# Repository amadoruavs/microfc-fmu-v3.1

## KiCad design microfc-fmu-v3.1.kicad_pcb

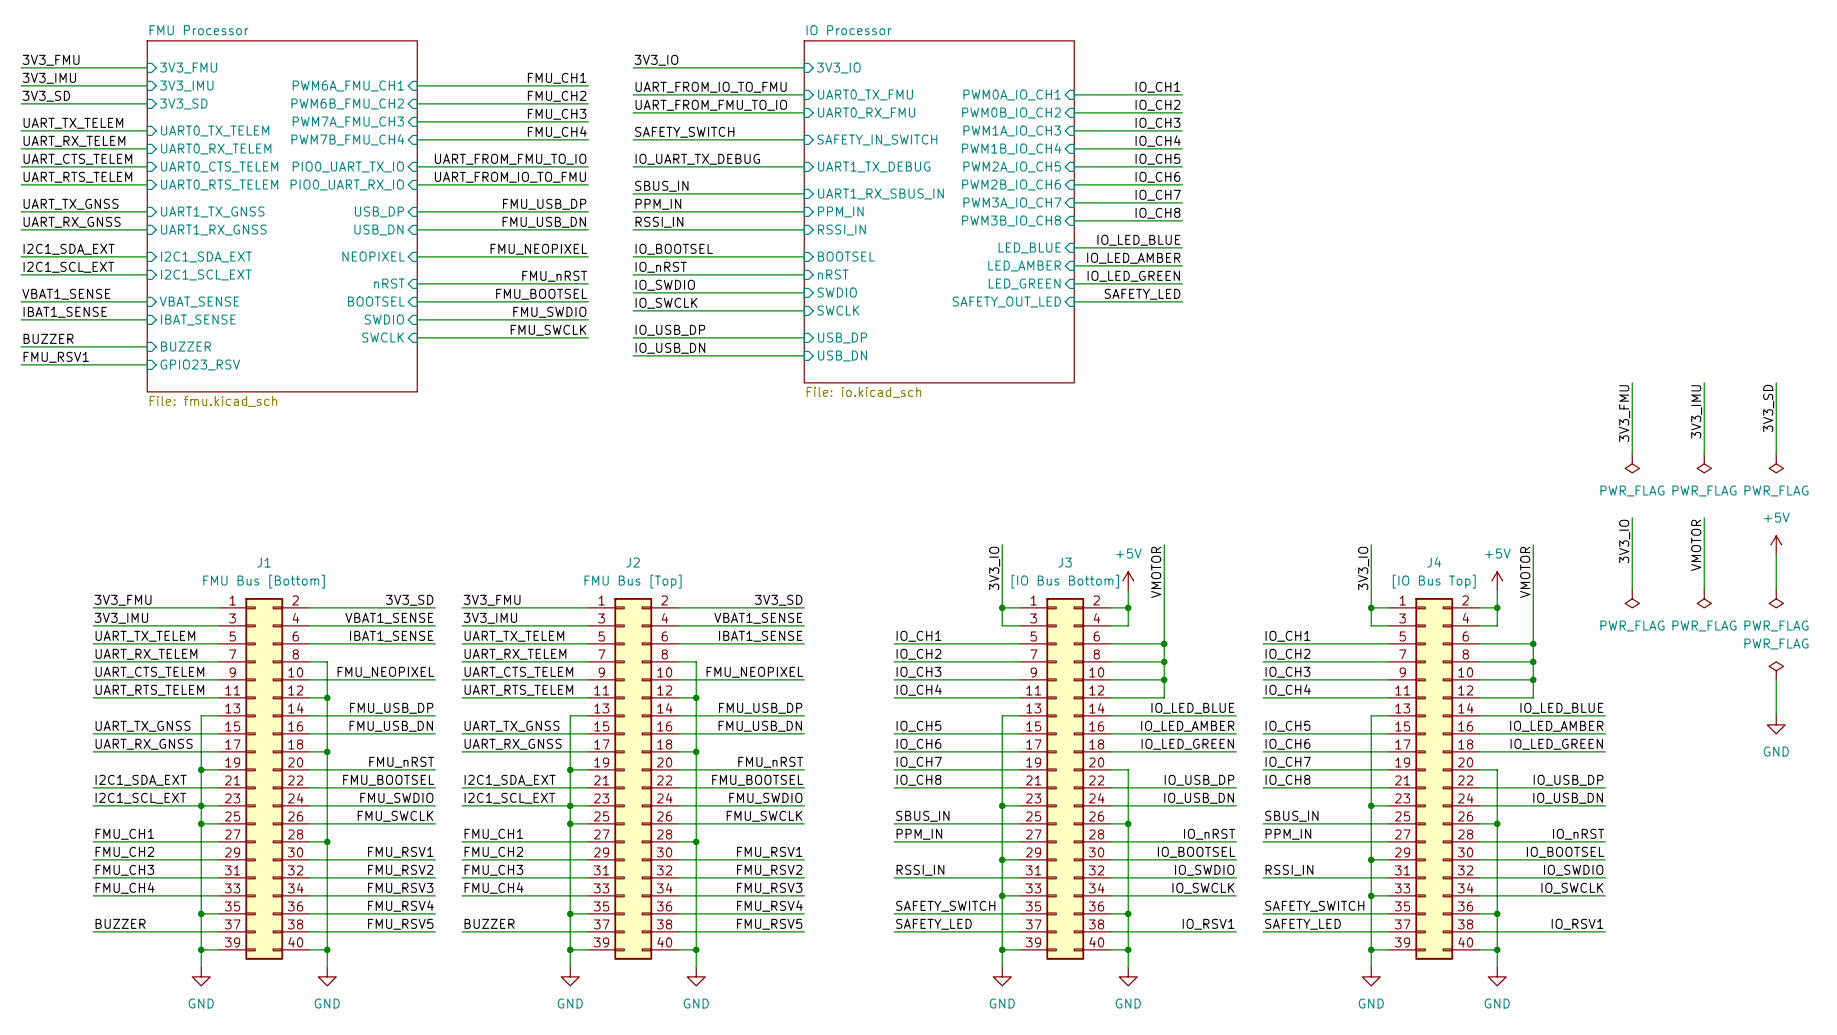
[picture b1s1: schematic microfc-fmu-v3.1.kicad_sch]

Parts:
J1: FMU Bus [Bottom]; HRS_DF40C-40DP-0.4V(51)
J2: FMU Bus [Top]; HIROSE_DF40C-40DS-0.4V(51)
J3: [IO Bus Bottom]; HRS_DF40C-40DP-0.4V(51)
J4: [IO Bus Top]; HIROSE_DF40C-40DS-0.4V(51)

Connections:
+5V: J3.2, J3.4, J4.2, J4.4
/3V3_FMU: J1.1, J2.1; also elsewhere on the board
/3V3_IMU: J1.3, J2.3; also elsewhere on the board
/3V3_IO: J3.1, J3.3, J4.1, J4.3; also elsewhere on the board
/3V3_SD: J1.2, J2.2; also elsewhere on the board
/BUZZER: J1.37, J2.37; also elsewhere on the board
/FMU_BOOTSEL: J1.22, J2.22; also elsewhere on the board
/FMU_CH1: J1.27, J2.27; also elsewhere on the board
/FMU_CH2: J1.29, J2.29; also elsewhere on the board
/FMU_CH3: J1.31, J2.31; also elsewhere on the board
/FMU_CH4: J1.33, J2.33; also elsewhere on the board
/FMU_NEOPIXEL: J1.10, J2.10; also elsewhere on the board
/FMU_RSV1: J1.30, J2.30; also elsewhere on the board
/FMU_RSV2: J1.32, J2.32
/FMU_RSV3: J1.34, J2.34
/FMU_RSV4: J1.36, J2.36
/FMU_RSV5: J1.38, J2.38
/FMU_SWCLK: J1.26, J2.26; also elsewhere on the board
/FMU_SWDIO: J1.24, J2.24; also elsewhere on the board
/FMU_USB_DN: J1.16, J2.16; also elsewhere on the board
/FMU_USB_DP: J1.14, J2.14; also elsewhere on the board
/FMU_nRST: J1.20, J2.20; also elsewhere on the board
/I2C1_SDA_EXT: J1.21, J2.21; also elsewhere on the board
/IO_BOOTSEL: J3.30, J4.30; also elsewhere on the board
/IO_CH1: J3.5, J4.5; also elsewhere on the board
/IO_CH2: J3.7, J4.7; also elsewhere on the board
/IO_CH3: J3.9, J4.9; also elsewhere on the board
/IO_CH4: J3.11, J4.11; also elsewhere on the board
/IO_CH5: J3.15, J4.15; also elsewhere on the board
/IO_CH6: J3.17, J4.17; also elsewhere on the board
/IO_CH7: J3.19, J4.19; also elsewhere on the board
/IO_CH8: J3.21, J4.21; also elsewhere on the board
/IO_LED_AMBER: J3.16, J4.16; also elsewhere on the board
/IO_LED_BLUE: J3.14, J4.14; also elsewhere on the board
/IO_LED_GREEN: J3.18, J4.18; also elsewhere on the board
/IO_RSV1: J3.38, J4.38
/IO_SWCLK: J3.34, J4.34; also elsewhere on the board
/IO_SWDIO: J3.32, J4.32; also elsewhere on the board
/IO_USB_DN: J3.24, J4.24; also elsewhere on the board
/IO_USB_DP: J3.22, J4.22; also elsewhere on the board
/IO_nRST: J3.28, J4.28; also elsewhere on the board
/PPM_IN: J3.27, J4.27; also elsewhere on the board
/RSSI_IN: J3.31, J4.31; also elsewhere on the board
/SAFETY_LED: J3.37, J4.37; also elsewhere on the board
/SAFETY_SWITCH: J3.35, J4.35; also elsewhere on the board
/SBUS_IN: J3.25, J4.25; also elsewhere on the board
/UART_CTS_TELEM: J1.9, J2.9; also elsewhere on the board
/UART_RTS_TELEM: J1.11, J2.11; also elsewhere on the board
/UART_RX_GNSS: J1.17, J2.17; also elsewhere on the board
/UART_RX_TELEM: J1.7, J2.7; also elsewhere on the board
/UART_TX_GNSS: J1.15, J2.15; also elsewhere on the board
/UART_TX_TELEM: J1.5, J2.5; also elsewhere on the board
/VMOTOR: J3.6, J3.8, J3.10, J3.12, J4.6, J4.8, J4.10, J4.12

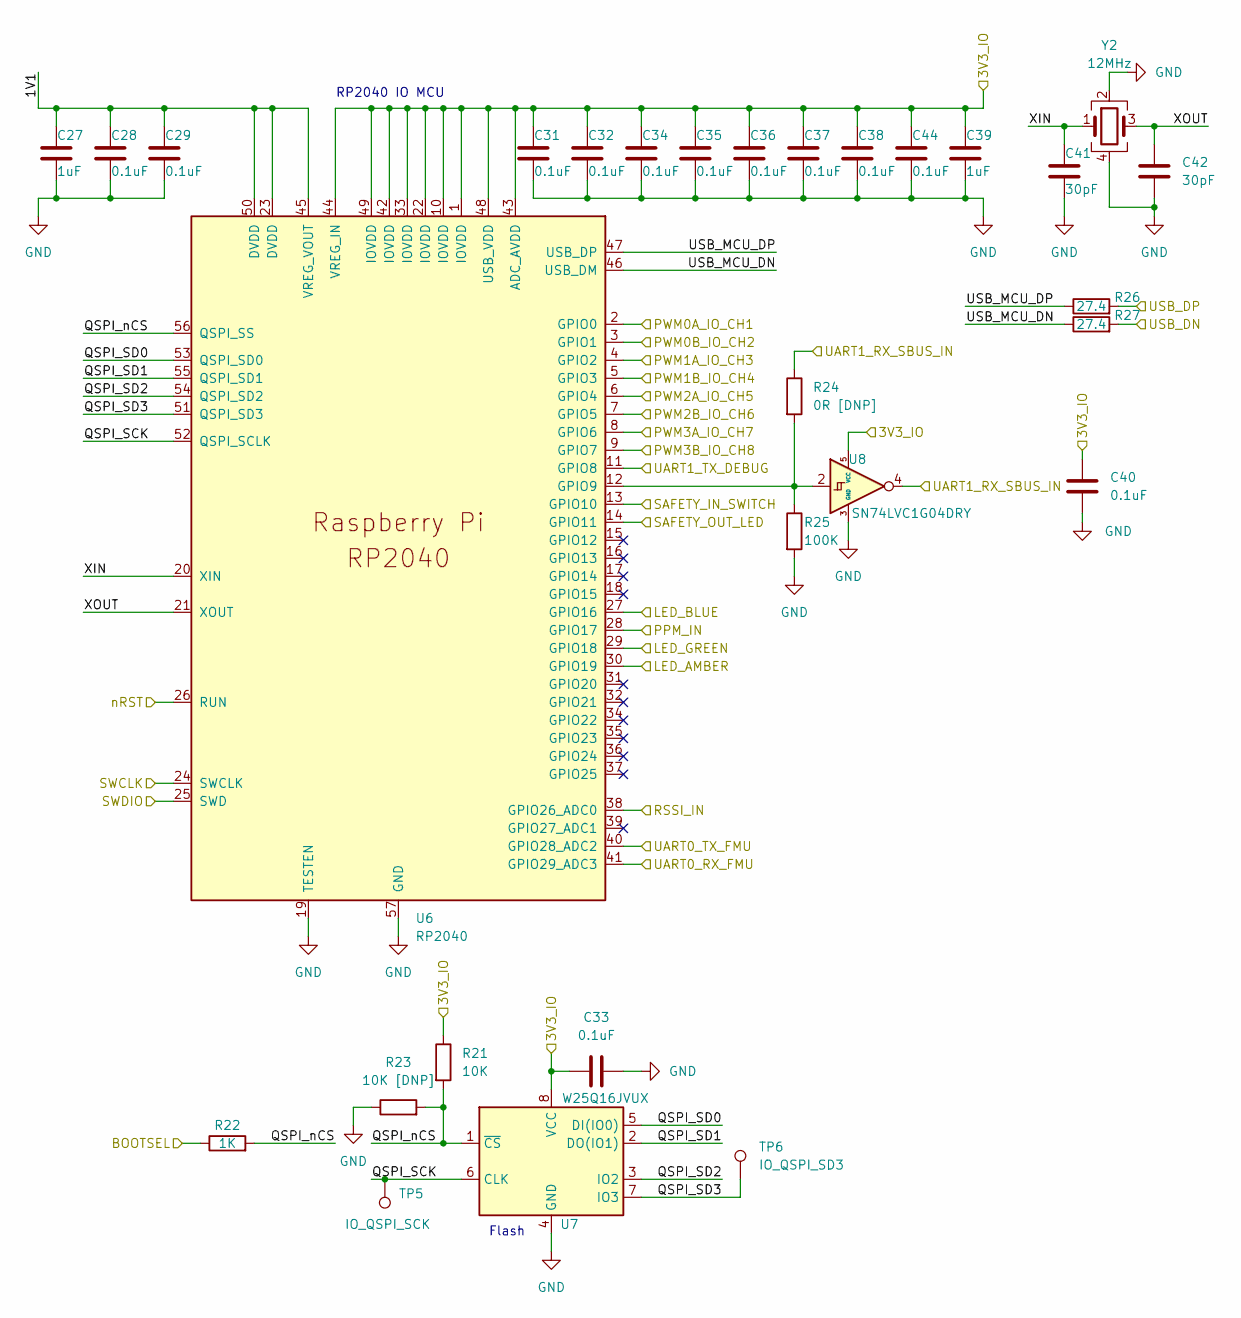
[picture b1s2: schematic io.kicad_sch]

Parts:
C27, C39: 1uF; C_0402_1005Metric; LCSC C52923
C28, C29, C31, C32, C33, C34, C35, C36, C37, C38, C44: 0.1uF; C_0402_1005Metric; LCSC C1525
C40: 0.1uF; C_0402_1005Metric
C41, C42: 30pF; C_0402_1005Metric; LCSC C1557
R21: 10K; R_0402_1005Metric; LCSC C25744
R22: 1K; R_0402_1005Metric; LCSC C25744
R23: 10K [DNP]; R_0402_1005Metric
R24: 0R [DNP]; R_0402_1005Metric
R25: 100K; R_0402_1005Metric
R26, R27: 27.4; R_0402_1005Metric
TP5: IO_QSPI_SCK; TestPoint_Pad_D1.0mm
TP6: IO_QSPI_SD3; TestPoint_Pad_D1.0mm
U6: RP2040; RP2040-QFN-56; LCSC C2040
U7: W25Q16JVUX; 8-USON; LCSC C2441425
U8: SN74LVC1G04DRY; SOT-553
Y2: 12MHz; Crystal_SMD_2520-4Pin_2.5x2.0mm

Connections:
/3V3_IO: C31.1, C32.1, C33.1, C34.1, C35.1, C36.1, C37.1, C38.1, C39.1, C40.2, C44.1, R21.1, U6.1 (IOVDD), U6.10 (IOVDD), U6.22 (IOVDD), U6.33 (IOVDD), U6.42 (IOVDD), U6.43 (ADC_AVDD), U6.44 (VREG_IN), U6.48 (USB_VDD), U6.49 (IOVDD), U7.8 (VCC), U8.5 (VCC); also elsewhere on the board
/IO Processor/1V1: C27.1, C28.1, C29.1, U6.23 (DVDD), U6.45 (VREG_VOUT), U6.50 (DVDD)
/IO Processor/QSPI_SCK: TP5.1, U6.52 (QSPI_SCLK), U7.6 (CLK)
/IO Processor/QSPI_SD0: U6.53 (QSPI_SD0), U7.5 (DI(IO0))
/IO Processor/QSPI_SD1: U6.55 (QSPI_SD1), U7.2 (DO(IO1))
/IO Processor/QSPI_SD2: U6.54 (QSPI_SD2), U7.3 (IO2)
/IO Processor/QSPI_SD3: TP6.1, U6.51 (QSPI_SD3), U7.7 (IO3)
/IO Processor/QSPI_nCS: R21.2, R22.2, R23.2, U6.56 (QSPI_SS), U7.1 (~CS)
/IO Processor/USB_MCU_DN: R27.1, U6.46 (USB_DM)
/IO Processor/USB_MCU_DP: R26.1, U6.47 (USB_DP)
/IO Processor/XIN: C41.1, U6.20 (XIN), Y2.1
/IO Processor/XOUT: C42.1, U6.21 (XOUT), Y2.3
/IO_BOOTSEL: R22.1; also elsewhere on the board
/IO_CH1: U6.2 (GPIO0); also elsewhere on the board
/IO_CH2: U6.3 (GPIO1); also elsewhere on the board
/IO_CH3: U6.4 (GPIO2); also elsewhere on the board
/IO_CH4: U6.5 (GPIO3); also elsewhere on the board
/IO_CH5: U6.6 (GPIO4); also elsewhere on the board
/IO_CH6: U6.7 (GPIO5); also elsewhere on the board
/IO_CH7: U6.8 (GPIO6); also elsewhere on the board
/IO_CH8: U6.9 (GPIO7); also elsewhere on the board
/IO_LED_AMBER: U6.30 (GPIO19); also elsewhere on the board
/IO_LED_BLUE: U6.27 (GPIO16); also elsewhere on the board
/IO_LED_GREEN: U6.29 (GPIO18); also elsewhere on the board
/IO_SWCLK: U6.24 (SWCLK); also elsewhere on the board
/IO_SWDIO: U6.25 (SWD); also elsewhere on the board
/IO_UART_TX_DEBUG: U6.11 (GPIO8)
/IO_USB_DN: R27.2; also elsewhere on the board
/IO_USB_DP: R26.2; also elsewhere on the board
/IO_nRST: U6.26 (RUN); also elsewhere on the board
/PPM_IN: U6.28 (GPIO17); also elsewhere on the board
/RSSI_IN: U6.38 (GPIO26_ADC0); also elsewhere on the board
/SAFETY_LED: U6.14 (GPIO11); also elsewhere on the board
/SAFETY_SWITCH: U6.13 (GPIO10); also elsewhere on the board
/SBUS_IN: R24.1, U8.4; also elsewhere on the board
/UART_FROM_FMU_TO_IO: U6.41 (GPIO29_ADC3); also elsewhere on the board
/UART_FROM_IO_TO_FMU: U6.40 (GPIO28_ADC2); also elsewhere on the board
unnamed: R24.2, R25.1, U6.12 (GPIO9), U8.2

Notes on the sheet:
RP2040 IO MCU
Flash

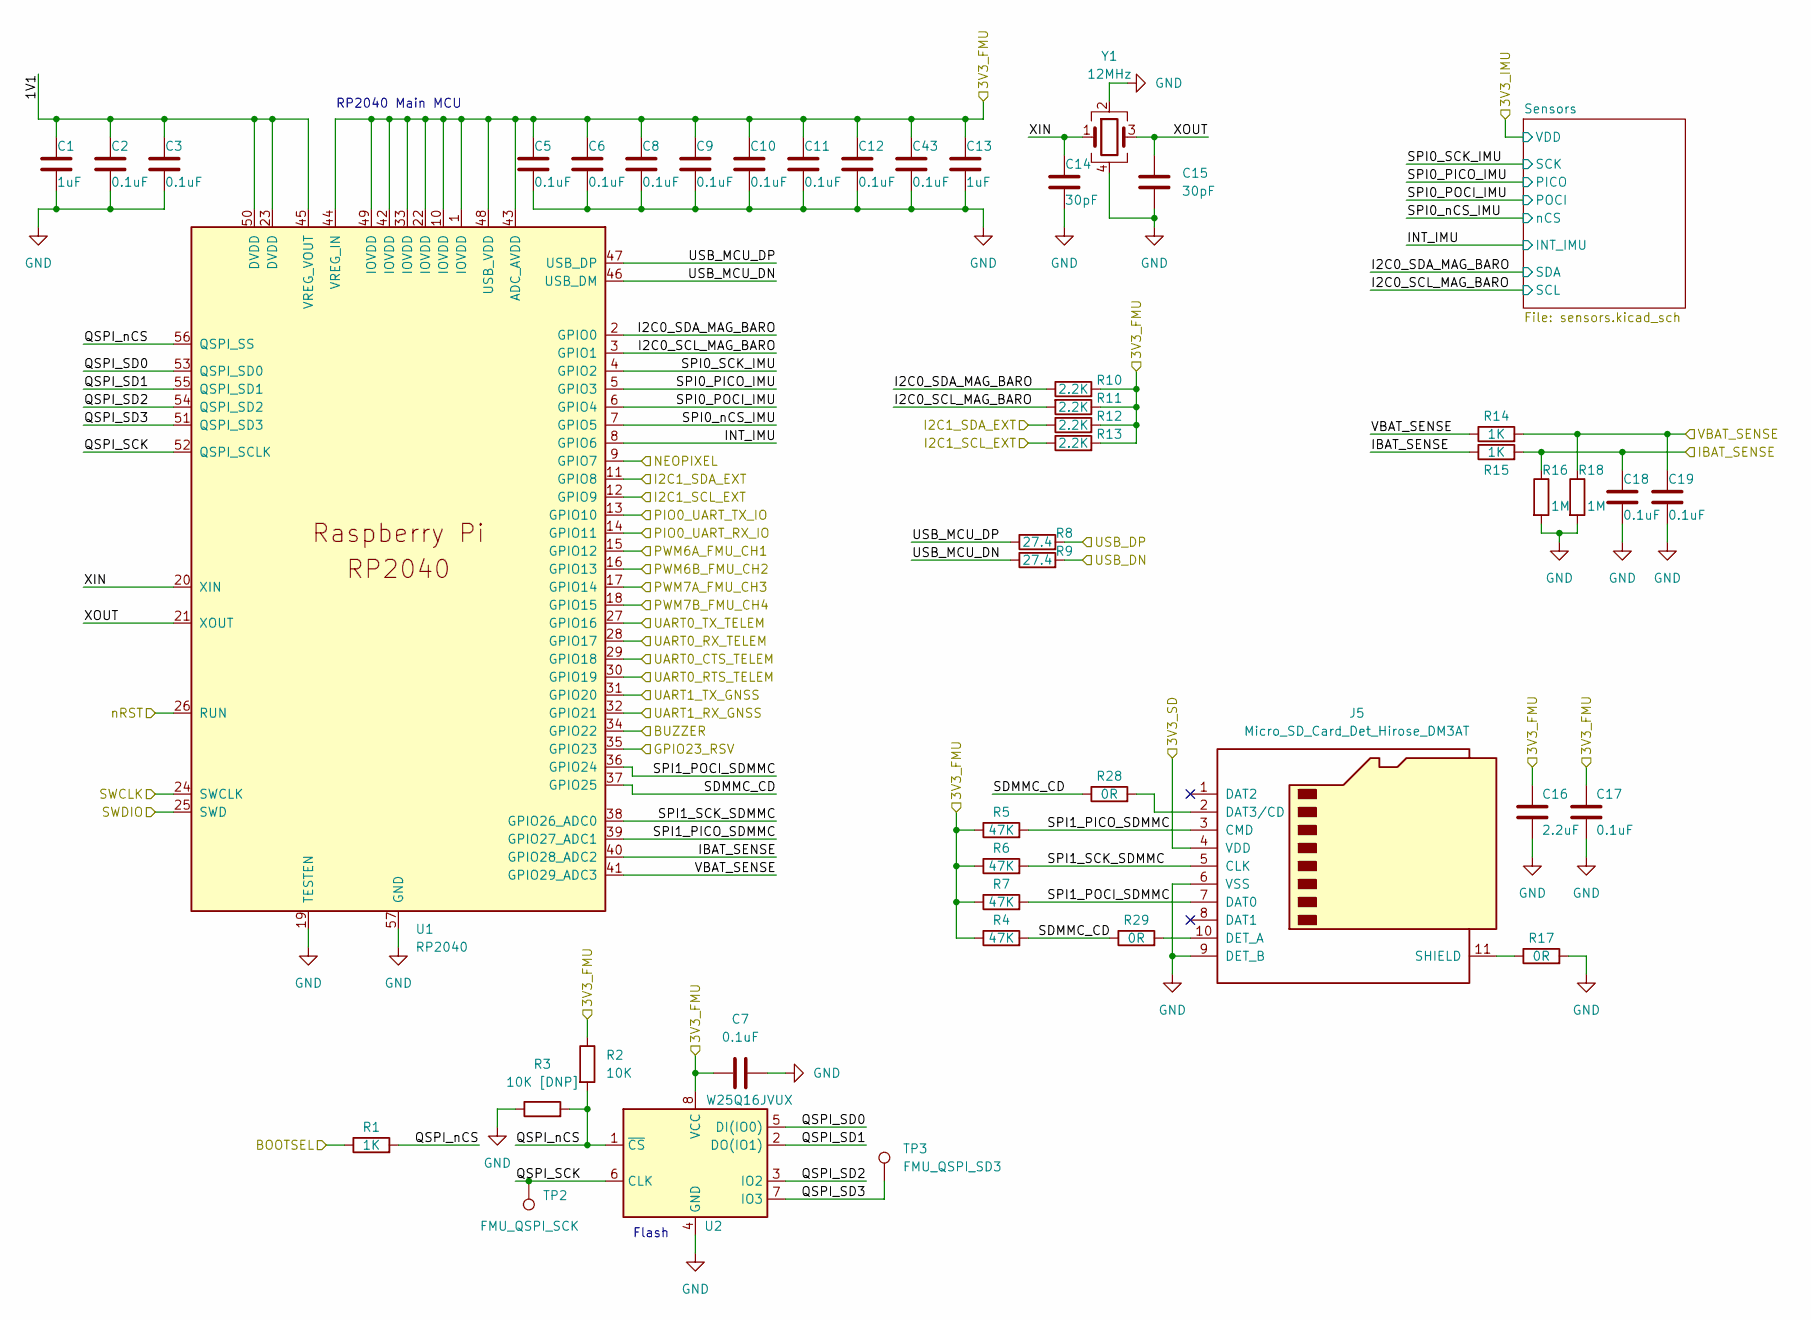
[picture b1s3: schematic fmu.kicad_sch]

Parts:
C1, C13: 1uF; C_0402_1005Metric; LCSC C52923
C2, C3, C5, C6, C7, C8, C9, C10, C11, C12, C43: 0.1uF; C_0402_1005Metric; LCSC C1525
C14, C15: 30pF; C_0402_1005Metric; LCSC C1557
C16: 2.2uF; C_0402_1005Metric
C17, C18, C19: 0.1uF; C_0402_1005Metric
J5: Micro_SD_Card_Det_Hirose_DM3AT; microSD_HC_Hirose_DM3AT-SF-PEJM5
R1: 1K; R_0402_1005Metric; LCSC C25744
R2: 10K; R_0402_1005Metric; LCSC C25744
R3: 10K [DNP]; R_0402_1005Metric
R4, R5, R6, R7: 47K; R_0402_1005Metric
R8, R9: 27.4; R_0402_1005Metric
R10, R11, R12, R13: 2.2K; R_0402_1005Metric; LCSC C25900
R14, R15: 1K; R_0402_1005Metric
R16, R18: 1M; R_0402_1005Metric
R17, R28, R29: 0R; R_0402_1005Metric
TP2: FMU_QSPI_SCK; TestPoint_Pad_D1.0mm
TP3: FMU_QSPI_SD3; TestPoint_Pad_D1.0mm
U1: RP2040; RP2040-QFN-56; LCSC C2040
U2: W25Q16JVUX; 8-USON; LCSC C2441425
Y1: 12MHz; Crystal_SMD_2520-4Pin_2.5x2.0mm

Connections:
/3V3_FMU: C5.1, C6.1, C7.1, C8.1, C9.1, C10.1, C11.1, C12.1, C13.1, C16.1, C17.1, C43.1, R2.1, R4.1, R5.1, R6.1, R7.1, R10.2, R11.1, R12.2, R13.2, U1.1 (IOVDD), U1.10 (IOVDD), U1.22 (IOVDD), U1.33 (IOVDD), U1.42 (IOVDD), U1.43 (ADC_AVDD), U1.44 (VREG_IN), U1.48 (USB_VDD), U1.49 (IOVDD), U2.8 (VCC); also elsewhere on the board
/3V3_SD: J5.4 (VDD); also elsewhere on the board
/BUZZER: U1.34 (GPIO22); also elsewhere on the board
/FMU Processor/1V1: C1.1, C2.1, C3.1, U1.23 (DVDD), U1.45 (VREG_VOUT), U1.50 (DVDD)
/FMU Processor/I2C0_SCL_MAG_BARO: R11.2, U1.3 (GPIO1); also elsewhere on the board
/FMU Processor/I2C0_SDA_MAG_BARO: R10.1, U1.2 (GPIO0); also elsewhere on the board
/FMU Processor/INT_IMU: U1.8 (GPIO6); also elsewhere on the board
/FMU Processor/QSPI_SCK: TP2.1, U1.52 (QSPI_SCLK), U2.6 (CLK)
/FMU Processor/QSPI_SD0: U1.53 (QSPI_SD0), U2.5 (DI(IO0))
/FMU Processor/QSPI_SD1: U1.55 (QSPI_SD1), U2.2 (DO(IO1))
/FMU Processor/QSPI_SD2: U1.54 (QSPI_SD2), U2.3 (IO2)
/FMU Processor/QSPI_SD3: TP3.1, U1.51 (QSPI_SD3), U2.7 (IO3)
/FMU Processor/QSPI_nCS: R1.2, R2.2, R3.2, U1.56 (QSPI_SS), U2.1 (~CS)
/FMU Processor/SDMMC_CD: R4.2, R28.1, R29.1, U1.37 (GPIO25)
/FMU Processor/SPI0_PICO_IMU: U1.5 (GPIO3); also elsewhere on the board
/FMU Processor/SPI0_POCI_IMU: U1.6 (GPIO4); also elsewhere on the board
/FMU Processor/SPI0_SCK_IMU: U1.4 (GPIO2); also elsewhere on the board
/FMU Processor/SPI0_nCS_IMU: U1.7 (GPIO5); also elsewhere on the board
/FMU Processor/SPI1_PICO_SDMMC: J5.3 (CMD), R5.2, U1.39 (GPIO27_ADC1)
/FMU Processor/SPI1_POCI_SDMMC: J5.7 (DAT0), R7.2, U1.36 (GPIO24)
/FMU Processor/SPI1_SCK_SDMMC: J5.5 (CLK), R6.2, U1.38 (GPIO26_ADC0)
/FMU Processor/USB_MCU_DN: R9.1, U1.46 (USB_DM)
/FMU Processor/USB_MCU_DP: R8.1, U1.47 (USB_DP)
/FMU Processor/XIN: C14.1, U1.20 (XIN), Y1.1
/FMU Processor/XOUT: C15.1, U1.21 (XOUT), Y1.3
/FMU_BOOTSEL: R1.1; also elsewhere on the board
/FMU_CH1: U1.15 (GPIO12); also elsewhere on the board
/FMU_CH2: U1.16 (GPIO13); also elsewhere on the board
/FMU_CH3: U1.17 (GPIO14); also elsewhere on the board
/FMU_CH4: U1.18 (GPIO15); also elsewhere on the board
/FMU_NEOPIXEL: U1.9 (GPIO7); also elsewhere on the board
/FMU_RSV1: U1.35 (GPIO23); also elsewhere on the board
/FMU_SWCLK: U1.24 (SWCLK); also elsewhere on the board
/FMU_SWDIO: U1.25 (SWD); also elsewhere on the board
/FMU_USB_DN: R9.2; also elsewhere on the board
/FMU_USB_DP: R8.2; also elsewhere on the board
/FMU_nRST: U1.26 (RUN); also elsewhere on the board
/I2C1_SDA_EXT: R12.1, U1.11 (GPIO8); also elsewhere on the board
/UART_CTS_TELEM: U1.29 (GPIO18); also elsewhere on the board
/UART_FROM_FMU_TO_IO: U1.13 (GPIO10); also elsewhere on the board
/UART_FROM_IO_TO_FMU: U1.14 (GPIO11); also elsewhere on the board
/UART_RTS_TELEM: U1.30 (GPIO19); also elsewhere on the board
/UART_RX_GNSS: U1.32 (GPIO21); also elsewhere on the board
/UART_RX_TELEM: U1.28 (GPIO17); also elsewhere on the board
/UART_TX_GNSS: U1.31 (GPIO20); also elsewhere on the board
/UART_TX_TELEM: U1.27 (GPIO16); also elsewhere on the board
unnamed: J5.2 (DAT3/CD), R28.2
unnamed: J5.10 (DET_A), R29.2
unnamed: J5.11 (SHIELD), R17.1

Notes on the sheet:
RP2040 Main MCU
Flash

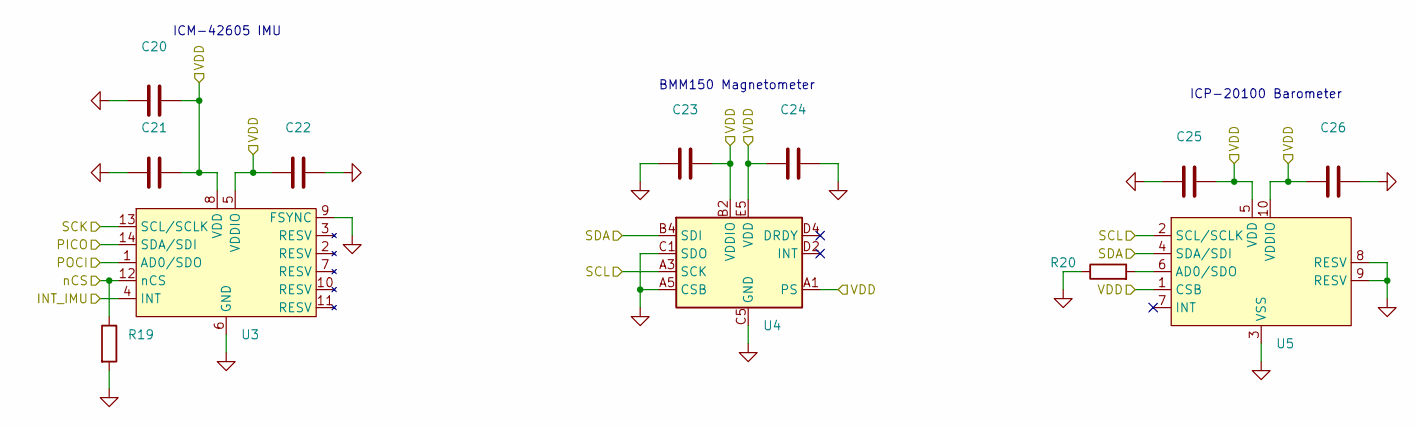
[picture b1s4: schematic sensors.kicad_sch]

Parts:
C20: LCSC C23733
C21, C25: LCSC C1525
C22, C26: LCSC C15195
C23, C24: (no value)
R19, R20: (no value)
U3, U4, U5: (no value)

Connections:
/3V3_IMU: C20.2, C21.2, C22.1, C23.2, C24.1, C25.2, C26.1, U3.5 (VDDIO), U3.8 (VDD), U4.A1 (PS), U4.B2 (VDDIO), U4.E5 (VDD), U5.1 (CSB), U5.5 (VDD), U5.10 (VDDIO); also elsewhere on the board
/FMU Processor/I2C0_SCL_MAG_BARO: U4.A3 (SCK), U5.2 (SCL/SCLK); also elsewhere on the board
/FMU Processor/I2C0_SDA_MAG_BARO: U4.B4 (SDI), U5.4 (SDA/SDI); also elsewhere on the board
/FMU Processor/INT_IMU: U3.4 (INT); also elsewhere on the board
/FMU Processor/SPI0_PICO_IMU: U3.14 (SDA/SDI); also elsewhere on the board
/FMU Processor/SPI0_POCI_IMU: U3.1 (AD0/SDO); also elsewhere on the board
/FMU Processor/SPI0_SCK_IMU: U3.13 (SCL/SCLK); also elsewhere on the board
/FMU Processor/SPI0_nCS_IMU: R19.1, U3.12 (nCS); also elsewhere on the board
unnamed: R20.2, U5.6 (AD0/SDO)

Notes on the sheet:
ICM-42605 IMU
ICP-20100 Barometer
BMM150 Magnetometer

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
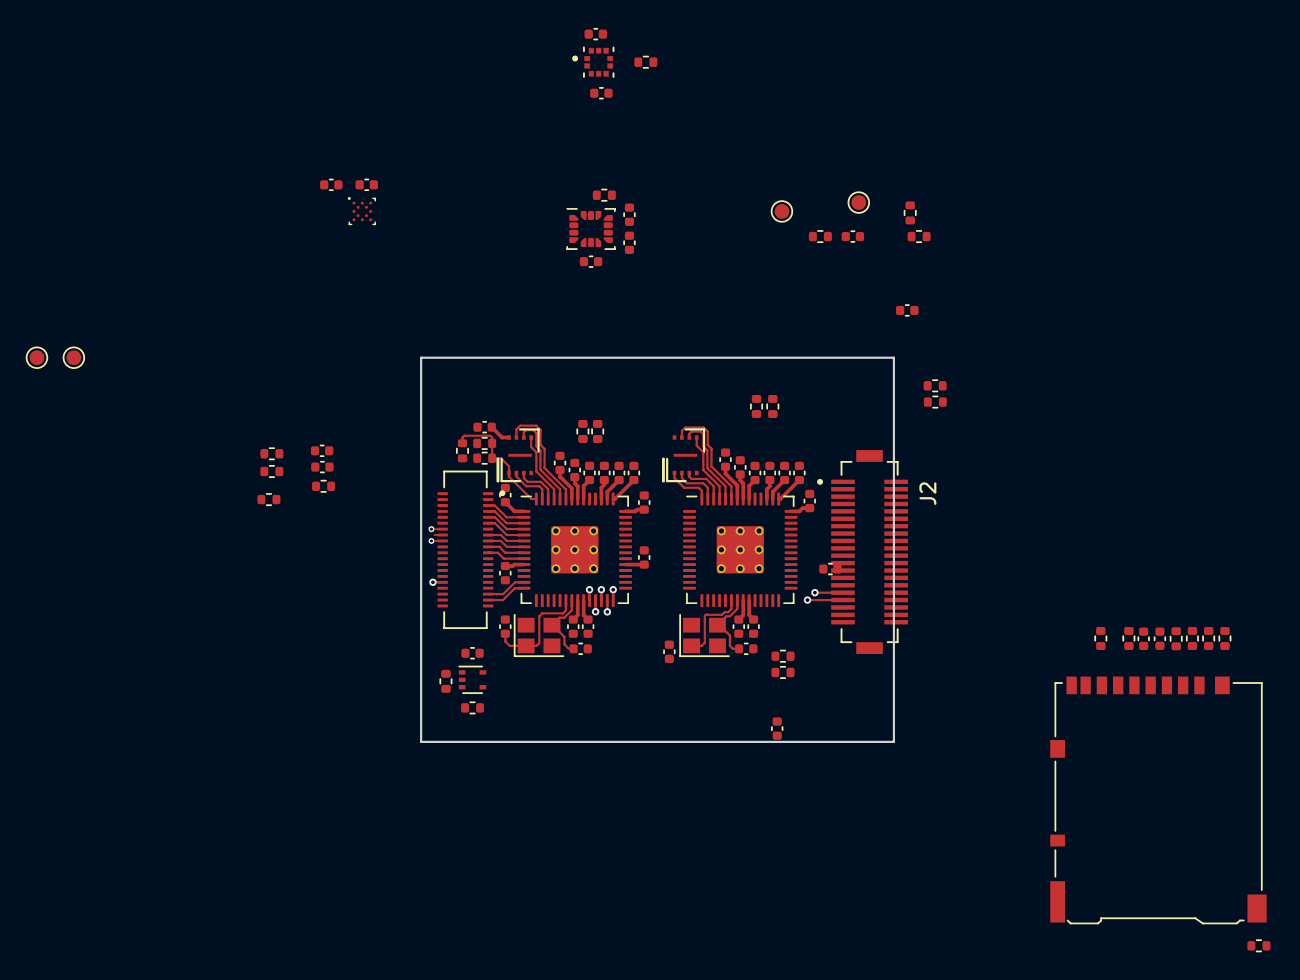
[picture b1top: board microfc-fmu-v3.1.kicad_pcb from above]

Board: 2 copper layers, 32.0 x 26.0 mm, 88 parts (0 on the bottom side), 92 nets.

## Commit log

2022-06-29 Add standard libraries submodule
2022-06-29 gitignore: add auto saved files
2022-06-29 schematic: add rp2040 pinout draft
2022-06-30 schematic: add peripherals and io
    * add fmu peripherals
    * add sensor suite
    * add io module
2022-06-30 schematic: add mezanine interfaces
2022-06-30 schematic: update power and fix errors
    * specify separate 3V3 lines
    * remove bus symbols due to incorrect usage
    * pass ERC
2022-06-30 schematic: fix mezanine typo
2022-06-30 add footprint assignments
2022-07-02 pcb layout draft, incomplete
2022-07-26 layout improvements, connector change
